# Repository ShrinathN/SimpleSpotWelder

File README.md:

# SimpleSpotWelder
I wanted a spot welder for 18650s so I designed this but then I didn't want a spot welder anymore so I never built it

This welder is designed to do
* Max 55J (more realistically 40J) solders
* Aprox 1000A for 100ms

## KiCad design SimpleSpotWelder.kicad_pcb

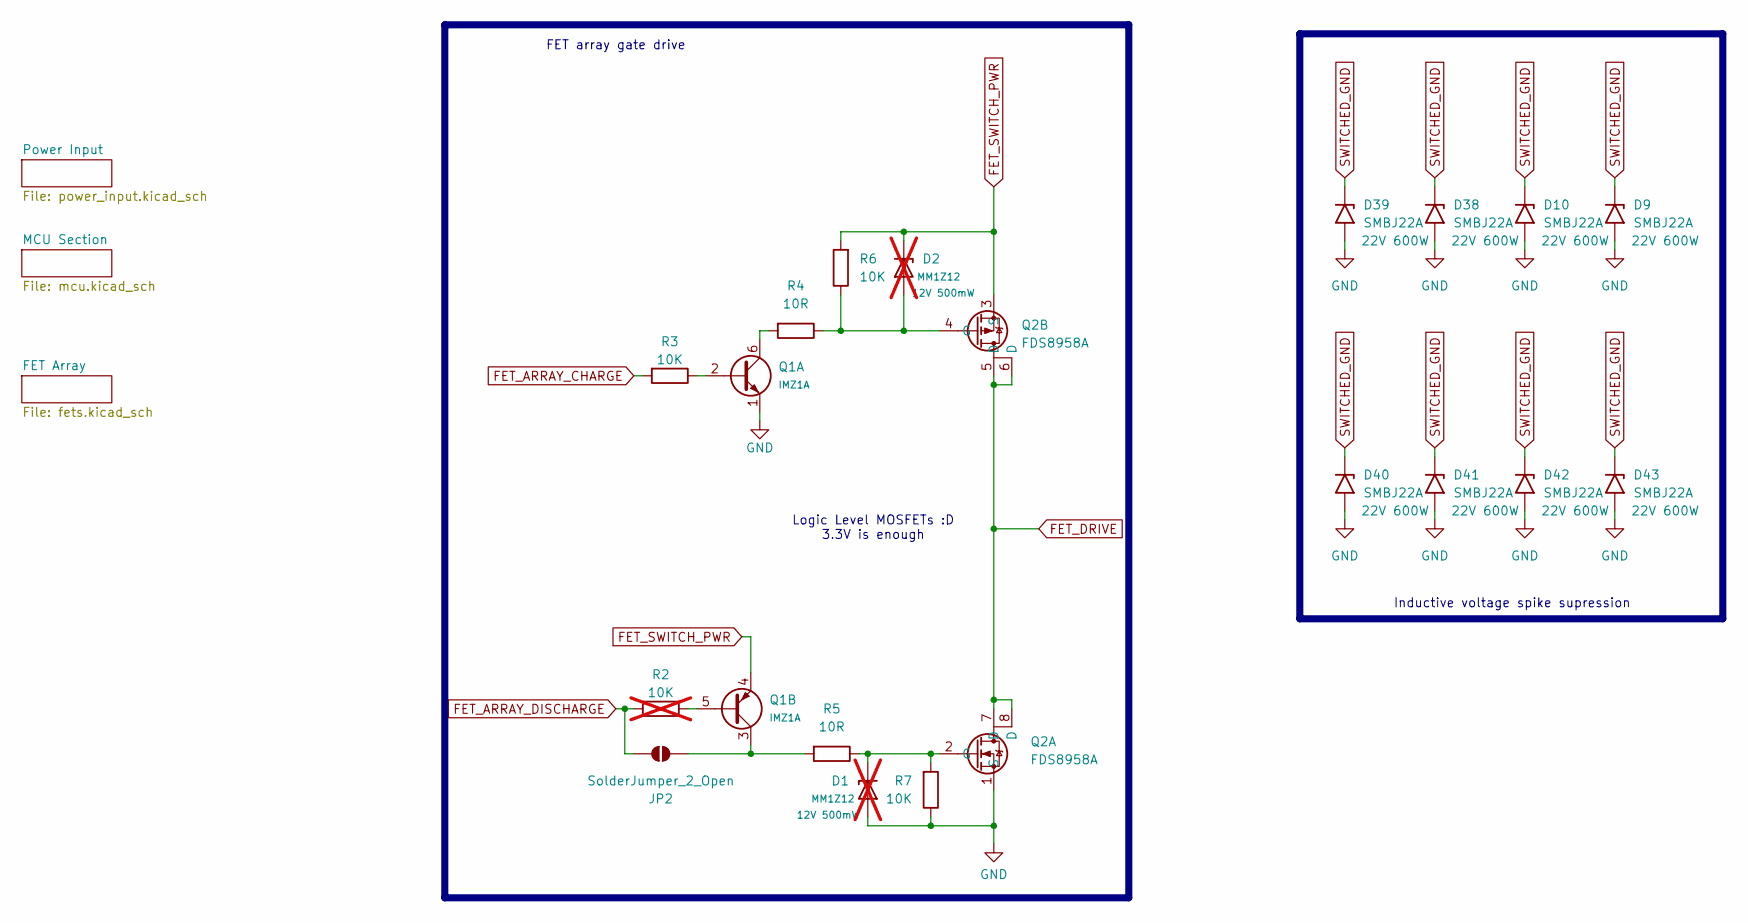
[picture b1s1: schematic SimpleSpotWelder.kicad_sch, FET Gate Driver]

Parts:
D1, D2: MM1Z12; D_SOD-123; Rating 12V 500mW; not fitted
D9, D10, D38, D39, D40, D41, D42, D43: SMBJ22A; D_SMB; Rating 22V 600W
JP2: SolderJumper_2_Open; SolderJumper-2_P1.3mm_Open_Pad1.0x1.5mm
Q1: IMZ1A; SOT-23-6
Q2: FDS8958A; SO-8_3.9x4.9mm_P1.27mm
R2: 10K; R_0805_2012Metric; not fitted
R3, R6, R7: 10K; R_0805_2012Metric
R4, R5: 10R; R_0805_2012Metric

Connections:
FET_ARRAY_CHARGE: R3.2; also elsewhere on the board
FET_ARRAY_DISCHARGE: JP2.2 (B), R2.2; also elsewhere on the board
FET_DRIVE: Q2.5 (D), Q2.6 (D), Q2.7 (D), Q2.8 (D); also elsewhere on the board
FET_SWITCH_PWR: D2.1 (K), Q1.4 (E2), Q2.3 (S), R6.2; also elsewhere on the board
GND: D1.2 (A), D9.2 (A2), D10.2 (A2), D38.2 (A2), D39.2 (A2), D40.2 (A2), D41.2 (A2), D42.2 (A2), D43.2 (A2), Q1.1 (E1), Q2.1 (S), R7.1; also elsewhere on the board
unnamed: D1.1 (K), Q2.2 (G), R5.1, R7.2
unnamed: D2.2 (A), Q2.4 (G), R4.1, R6.1
unnamed: JP2.1 (A), Q1.3 (C2), R5.2
unnamed: Q1.2 (B1), R3.1
unnamed: Q1.6 (C1), R4.2
unnamed: Q1.5 (B2), R2.1
SWITCHED_GND: D9.1 (A1), D10.1 (A1), D38.1 (A1), D39.1 (A1), D40.1 (A1), D41.1 (A1), D42.1 (A1), D43.1 (A1); also elsewhere on the board

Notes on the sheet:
Logic Level MOSFETs :D 3.3V is enough
Inductive voltage spike supression
FET array gate drive

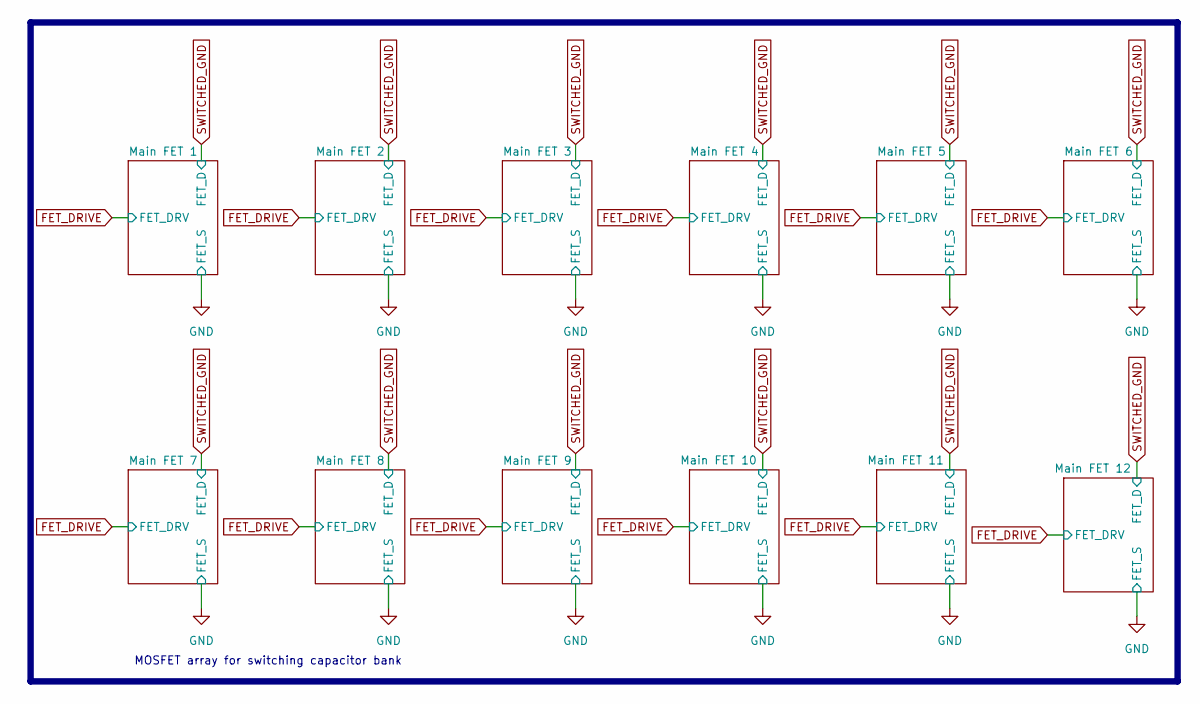
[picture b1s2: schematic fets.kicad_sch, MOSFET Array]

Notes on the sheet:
MOSFET array for switching capacitor bank

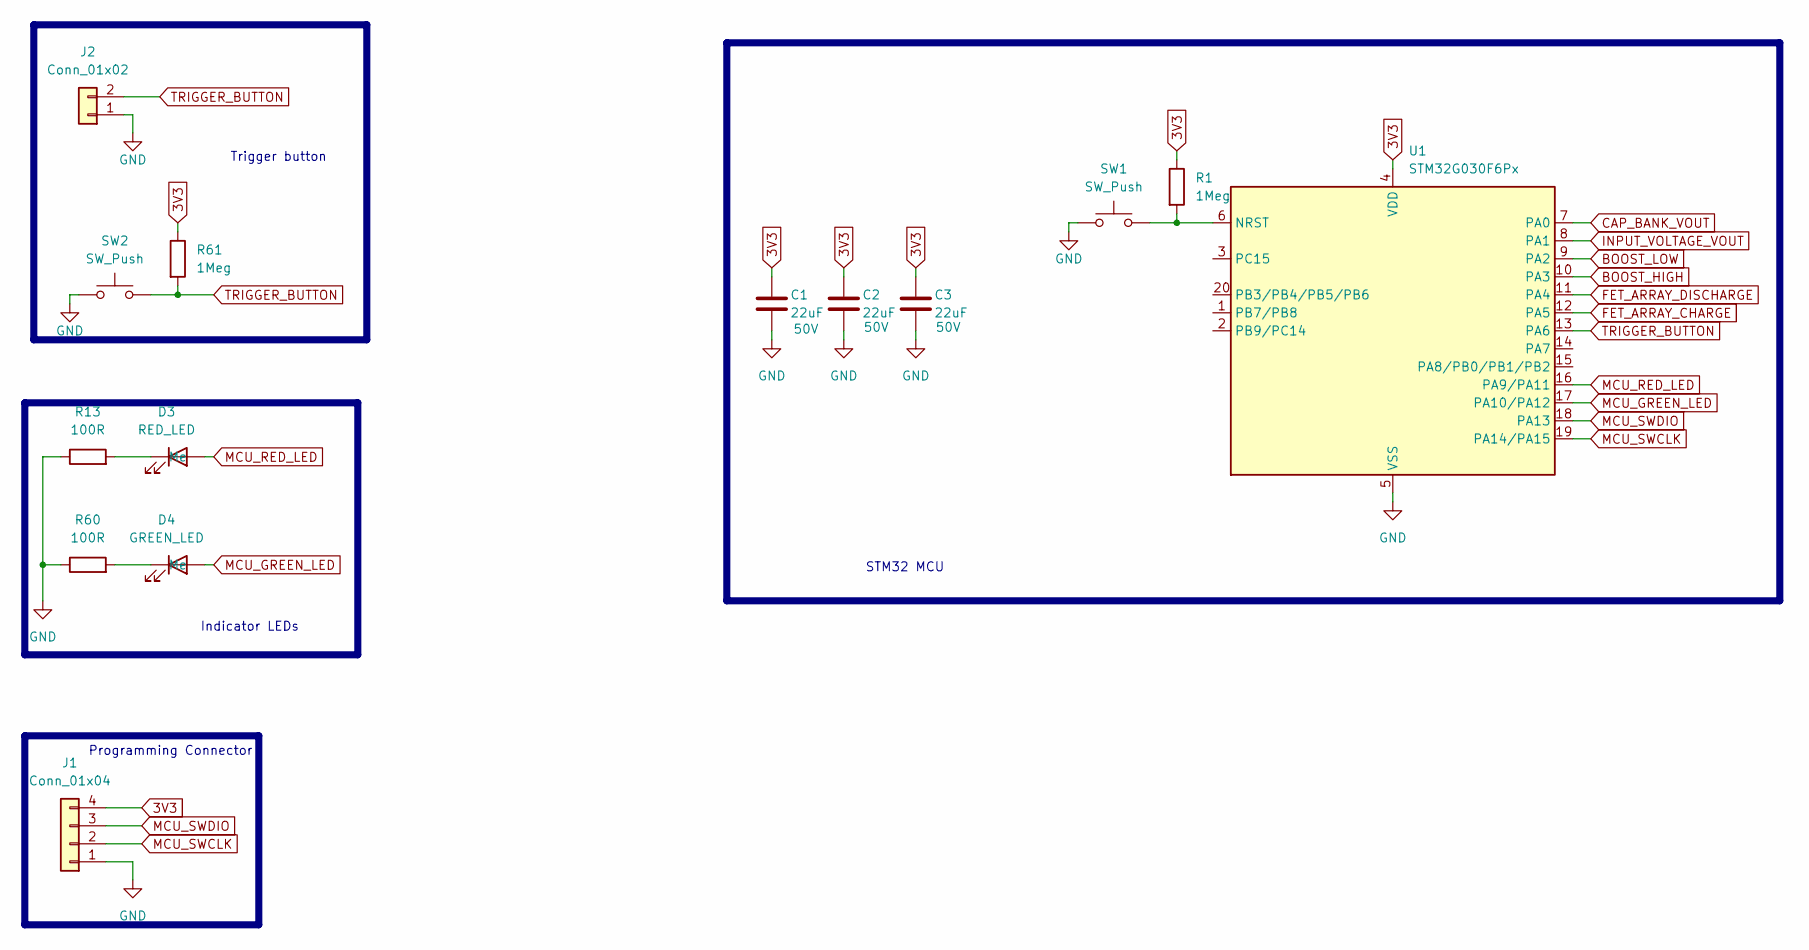
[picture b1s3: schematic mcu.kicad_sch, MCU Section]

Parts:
C1, C2, C3: 22uF; C_0805_2012Metric; Rating 50V
D3: RED_LED; LED_0805_2012Metric
D4: GREEN_LED; LED_0805_2012Metric
J1: Conn_01x04; PinSocket_1x04_P2.54mm_Vertical
J2: Conn_01x02; PinSocket_1x02_P2.54mm_Vertical
R1, R61: 1Meg; R_0805_2012Metric
R13, R60: 100R; R_0805_2012Metric
SW1, SW2: SW_Push; SW_Push_1P1T_XKB_TS-1187A
U1: STM32G030F6Px; TSSOP-20_4.4x6.5mm_P0.65mm

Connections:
3V3: C1.1, C2.1, C3.1, J1.4, R1.1, R61.1, U1.4 (VDD); also elsewhere on the board
BOOST_HIGH: U1.10 (PA3); also elsewhere on the board
BOOST_LOW: U1.9 (PA2); also elsewhere on the board
CAP_BANK_VOUT: U1.7 (PA0); also elsewhere on the board
FET_ARRAY_CHARGE: U1.12 (PA5); also elsewhere on the board
FET_ARRAY_DISCHARGE: U1.11 (PA4); also elsewhere on the board
GND: C1.2, C2.2, C3.2, J1.1, J2.1, R13.1, R60.1, SW1.1, SW2.1, U1.5 (VSS); also elsewhere on the board
INPUT_VOLTAGE_VOUT: U1.8 (PA1); also elsewhere on the board
MCU_GREEN_LED: D4.2 (A), U1.17 (PA10/PA12)
MCU_RED_LED: D3.2 (A), U1.16 (PA9/PA11)
MCU_SWCLK: J1.2, U1.19 (PA14/PA15)
MCU_SWDIO: J1.3, U1.18 (PA13)
unnamed: D3.1 (K), R13.2
unnamed: D4.1 (K), R60.2
unnamed: R1.2, SW1.2, U1.6 (NRST)
TRIGGER_BUTTON: J2.2, R61.2, SW2.2, U1.13 (PA6)

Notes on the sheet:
STM32 MCU
Indicator LEDs
Programming Connector
Trigger button

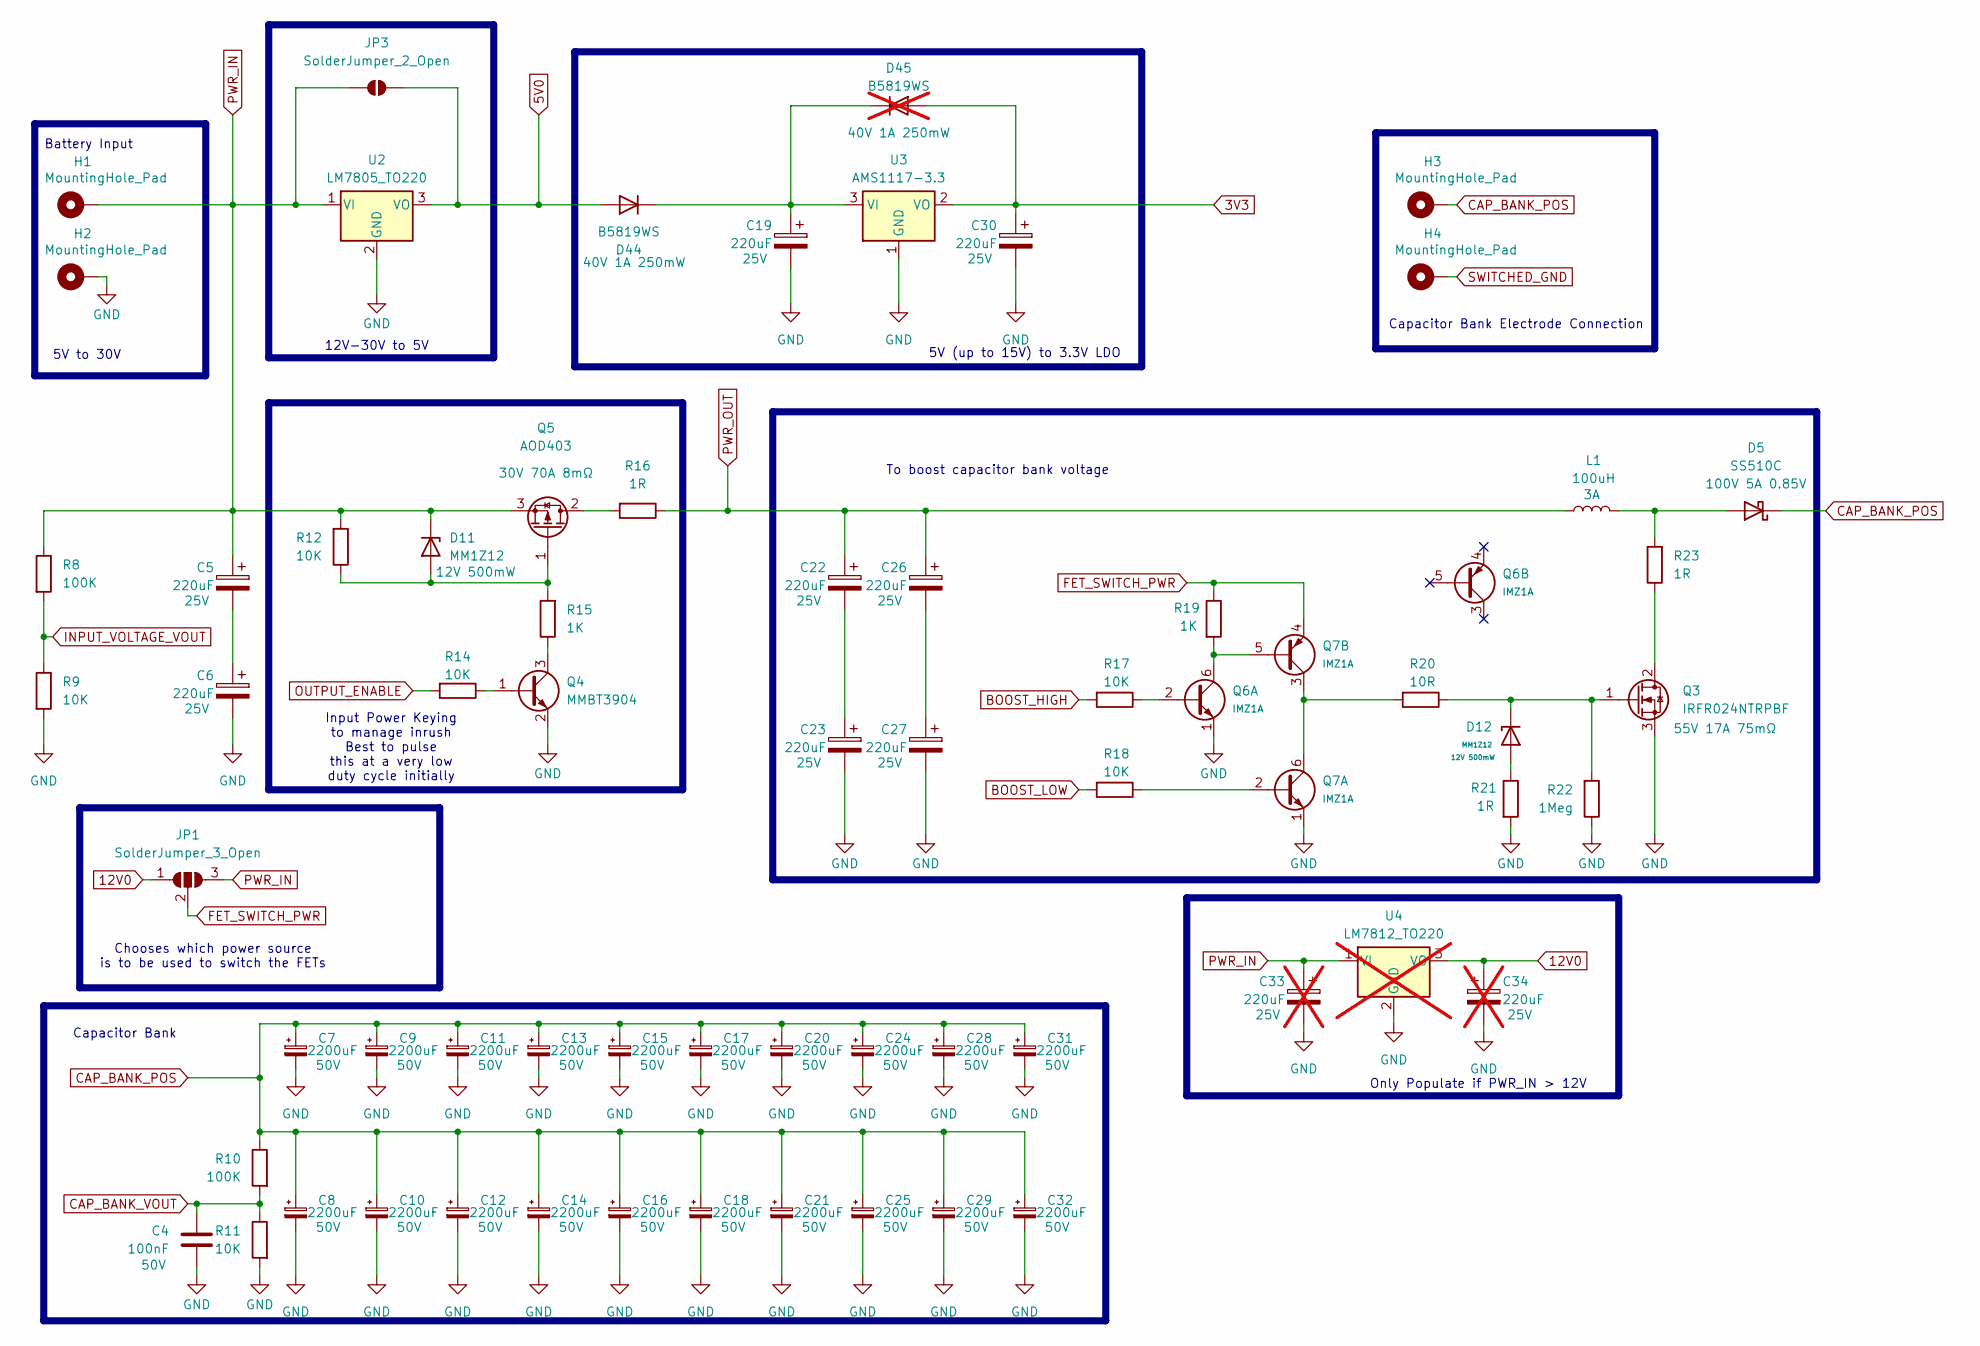
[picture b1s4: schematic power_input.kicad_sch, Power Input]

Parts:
C4: 100nF; C_0805_2012Metric; Rating 50V
C5, C6, C19, C22, C23, C26, C27, C30: 220uF; CP_Radial_D5.0mm_P2.00mm; Rating 25V
C7, C8, C9, C10, C11, C12, C13, C14, C15, C16, C17, C18, C20, C21, C24, C25, C28, C29, C31, C32: 2200uF; CP_Radial_D18.0mm_P7.50mm; Rating 50V
C33, C34: 220uF; CP_Radial_D5.0mm_P2.00mm; Rating 25V; not fitted
D5: SS510C; D_SMC; Rating 100V 5A 0.85V
D11, D12: MM1Z12; D_SOD-123; Rating 12V 500mW
D44: B5819WS; D_SOD-323; Rating 40V 1A 250mW
D45: B5819WS; D_SOD-323; Rating 40V 1A 250mW; not fitted
H1, H2, H3, H4: MountingHole_Pad; MountingHole_3.2mm_M3_Pad_Via
JP1: SolderJumper_3_Open; SolderJumper-3_P2.0mm_Open_TrianglePad1.0x1.5mm
JP3: SolderJumper_2_Open; SolderJumper-2_P1.3mm_Open_Pad1.0x1.5mm
L1: 100uH; L_Coilcraft_MSS1278H-XXX; Rating 3A
Q3: IRFR024NTRPBF; TO-252-2; Rating 55V 17A 75mΩ
Q4: MMBT3904; SOT-23
Q5: AOD403; TO-252-2; Rating 30V 70A 8mΩ
Q6, Q7: IMZ1A; SOT-23-6
R8, R10: 100K; R_0805_2012Metric
R9, R11, R12, R14, R17, R18: 10K; R_0805_2012Metric
R15, R19: 1K; R_0805_2012Metric
R16, R21, R23: 1R; R_0805_2012Metric
R20: 10R; R_0805_2012Metric
R22: 1Meg; R_0805_2012Metric
U2: LM7805_TO220; TO-220-3_Vertical
U3: AMS1117-3.3; SOT-223-3_TabPin2
U4: LM7812_TO220; TO-220-3_Vertical; not fitted

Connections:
3V3: C30.1, D45.2 (A), U3.2 (VO); also elsewhere on the board
5V0: D44.2 (A), JP3.2 (B), U2.3 (VO)
12V0: C34.1, JP1.1 (A), U4.3 (VO)
BOOST_HIGH: R17.2; also elsewhere on the board
BOOST_LOW: R18.2; also elsewhere on the board
CAP_BANK_POS: C7.1, C8.1, C9.1, C10.1, C11.1, C12.1, C13.1, C14.1, C15.1, C16.1, C17.1, C18.1, C20.1, C21.1, C24.1, C25.1, C28.1, C29.1, C31.1, C32.1, D5.1 (K), H3.1, R10.1
CAP_BANK_VOUT: C4.1, R10.2, R11.1; also elsewhere on the board
FET_SWITCH_PWR: JP1.2 (C), Q7.4 (E2), R19.1; also elsewhere on the board
GND: C4.2, C6.2, C7.2, C8.2, C9.2, C10.2, C11.2, C12.2, C13.2, C14.2, C15.2, C16.2, C17.2, C18.2, C19.2, C20.2, C21.2, C23.2, C24.2, C25.2, C27.2, C28.2, C29.2, C30.2, C31.2, C32.2, C33.2, C34.2, H2.1, Q3.3 (S), Q4.2 (E), Q6.1 (E1), Q7.1 (E1), R9.2, R11.2, R21.2, R22.1, U2.2 (GND), U3.1 (GND), U4.2 (GND); also elsewhere on the board
INPUT_VOLTAGE_VOUT: R8.2, R9.1; also elsewhere on the board
unnamed: C5.2, C6.1
unnamed: C22.2, C23.1
unnamed: C26.2, C27.1
unnamed: D5.2 (A), L1.2, R23.2
unnamed: D11.2 (A), Q5.1 (G), R12.1, R15.2
unnamed: D12.2 (A), R21.1
unnamed: D12.1 (K), Q3.1 (G), R20.1, R22.2
unnamed: C19.1, D44.1 (K), D45.1 (K), U3.3 (VI)
unnamed: Q3.2 (D), R23.1
unnamed: Q4.1 (B), R14.1
unnamed: Q4.3 (C), R15.1
unnamed: Q5.2 (D), R16.2
unnamed: Q6.2 (B1), R17.1
unnamed: Q6.6 (C1), Q7.5 (B2), R19.2
unnamed: Q7.2 (B1), R18.1
unnamed: Q7.3 (C2), Q7.6 (C1), R20.2
OUTPUT_ENABLE: R14.2
PWR_IN: C5.1, C33.1, D11.1 (K), H1.1, JP1.3 (B), JP3.1 (A), Q5.3 (S), R8.1, R12.2, U2.1 (VI), U4.1 (VI)
PWR_OUT: C22.1, C26.1, L1.1, R16.1
SWITCHED_GND: H4.1; also elsewhere on the board

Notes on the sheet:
Only Populate if PWR_IN > 12V
5V (up to 15V) to 3.3V LDO
To boost capacitor bank voltage
Battery Input
12V-30V to 5V
Capacitor Bank
Input Power Keying to manage inrush Best to pulse this at a very low duty cycle initially
Chooses which power source is to be used to switch the FETs
Capacitor Bank Electrode Connection
5V to 30V

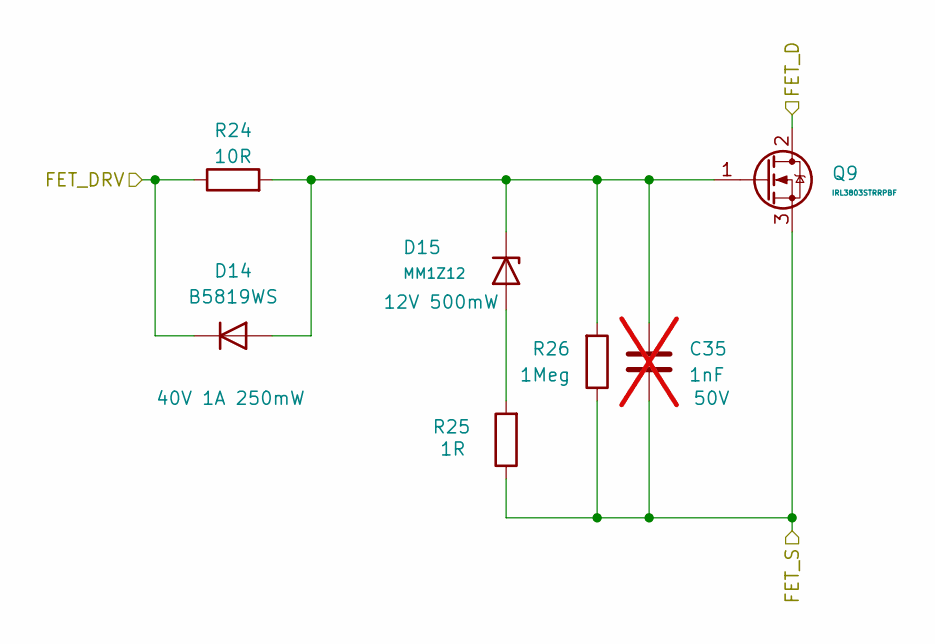
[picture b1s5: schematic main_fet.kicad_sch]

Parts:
C35: 1nF; C_0805_2012Metric; Rating 50V; not fitted
D14: B5819WS; D_SOD-323; Rating 40V 1A 250mW
D15: MM1Z12; D_SOD-123; Rating 12V 500mW
Q9: IRL3803STRRPBF; TO-263-2
R24: 10R; R_0805_2012Metric
R25: 1R; R_0805_2012Metric
R26: 1Meg; R_0805_2012Metric

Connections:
FET_DRIVE: D14.1 (K), R24.1; also elsewhere on the board
GND: C35.2, Q9.3 (S), R25.1, R26.1; also elsewhere on the board
unnamed: C35.1, D14.2 (A), D15.1 (K), Q9.1 (G), R24.2, R26.2
unnamed: D15.2 (A), R25.2
SWITCHED_GND: Q9.2 (D); also elsewhere on the board

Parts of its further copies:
C36, C37, C38, C39, C40, C41, C42, C43, C44, C45, C46: 1nF; C_0805_2012Metric; Rating 50V; not fitted
D16, D18, D20, D22, D24, D26, D28, D30, D32, D34, D36: B5819WS; D_SOD-323; Rating 40V 1A 250mW
D17, D19, D21, D23, D25, D27, D29, D31, D33, D35, D37: MM1Z12; D_SOD-123; Rating 12V 500mW
Q10, Q11, Q12, Q13, Q14, Q15, Q16, Q17, Q18, Q19, Q20: IRL3803STRRPBF; TO-263-2
R27, R30, R33, R36, R39, R42, R45, R48, R51, R54, R57: 10R; R_0805_2012Metric
R28, R31, R34, R37, R40, R43, R46, R49, R52, R55, R58: 1R; R_0805_2012Metric
R29, R32, R35, R38, R41, R44, R47, R50, R53, R56, R59: 1Meg; R_0805_2012Metric

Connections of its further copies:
FET_DRIVE: D16.1 (K), D18.1 (K), D20.1 (K), D22.1 (K), D24.1 (K), D26.1 (K), D28.1 (K), D30.1 (K), D32.1 (K), D34.1 (K), D36.1 (K), R27.1, R30.1, R33.1, R36.1, R39.1, R42.1, R45.1, R48.1, R51.1, R54.1, R57.1; also elsewhere on the board
GND: C36.2, C37.2, C38.2, C39.2, C40.2, C41.2, C42.2, C43.2, C44.2, C45.2, C46.2, Q10.3 (S), Q11.3 (S), Q12.3 (S), Q13.3 (S), Q14.3 (S), Q15.3 (S), Q16.3 (S), Q17.3 (S), Q18.3 (S), Q19.3 (S), Q20.3 (S), R28.1, R29.1, R31.1, R32.1, R34.1, R35.1, R37.1, R38.1, R40.1, R41.1, R43.1, R44.1, R46.1, R47.1, R49.1, R50.1, R52.1, R53.1, R55.1, R56.1, R58.1, R59.1; also elsewhere on the board
unnamed: C36.1, D16.2 (A), D17.1 (K), Q10.1 (G), R27.2, R29.2
unnamed: D17.2 (A), R28.2
unnamed: C37.1, D18.2 (A), D19.1 (K), Q11.1 (G), R30.2, R32.2
unnamed: D19.2 (A), R31.2
unnamed: C38.1, D20.2 (A), D21.1 (K), Q12.1 (G), R33.2, R35.2
unnamed: D21.2 (A), R34.2
unnamed: C39.1, D22.2 (A), D23.1 (K), Q13.1 (G), R36.2, R38.2
unnamed: D23.2 (A), R37.2
unnamed: C40.1, D24.2 (A), D25.1 (K), Q14.1 (G), R39.2, R41.2
unnamed: D25.2 (A), R40.2
unnamed: C41.1, D26.2 (A), D27.1 (K), Q15.1 (G), R42.2, R44.2
unnamed: D27.2 (A), R43.2
unnamed: C42.1, D28.2 (A), D29.1 (K), Q16.1 (G), R45.2, R47.2
unnamed: D29.2 (A), R46.2
unnamed: C43.1, D30.2 (A), D31.1 (K), Q17.1 (G), R48.2, R50.2
unnamed: D31.2 (A), R49.2
unnamed: C44.1, D32.2 (A), D33.1 (K), Q18.1 (G), R51.2, R53.2
unnamed: D33.2 (A), R52.2
unnamed: C45.1, D34.2 (A), D35.1 (K), Q19.1 (G), R54.2, R56.2
unnamed: D35.2 (A), R55.2
unnamed: C46.1, D36.2 (A), D37.1 (K), Q20.1 (G), R57.2, R59.2
unnamed: D37.2 (A), R58.2
SWITCHED_GND: Q10.2 (D), Q11.2 (D), Q12.2 (D), Q13.2 (D), Q14.2 (D), Q15.2 (D), Q16.2 (D), Q17.2 (D), Q18.2 (D), Q19.2 (D), Q20.2 (D); also elsewhere on the board

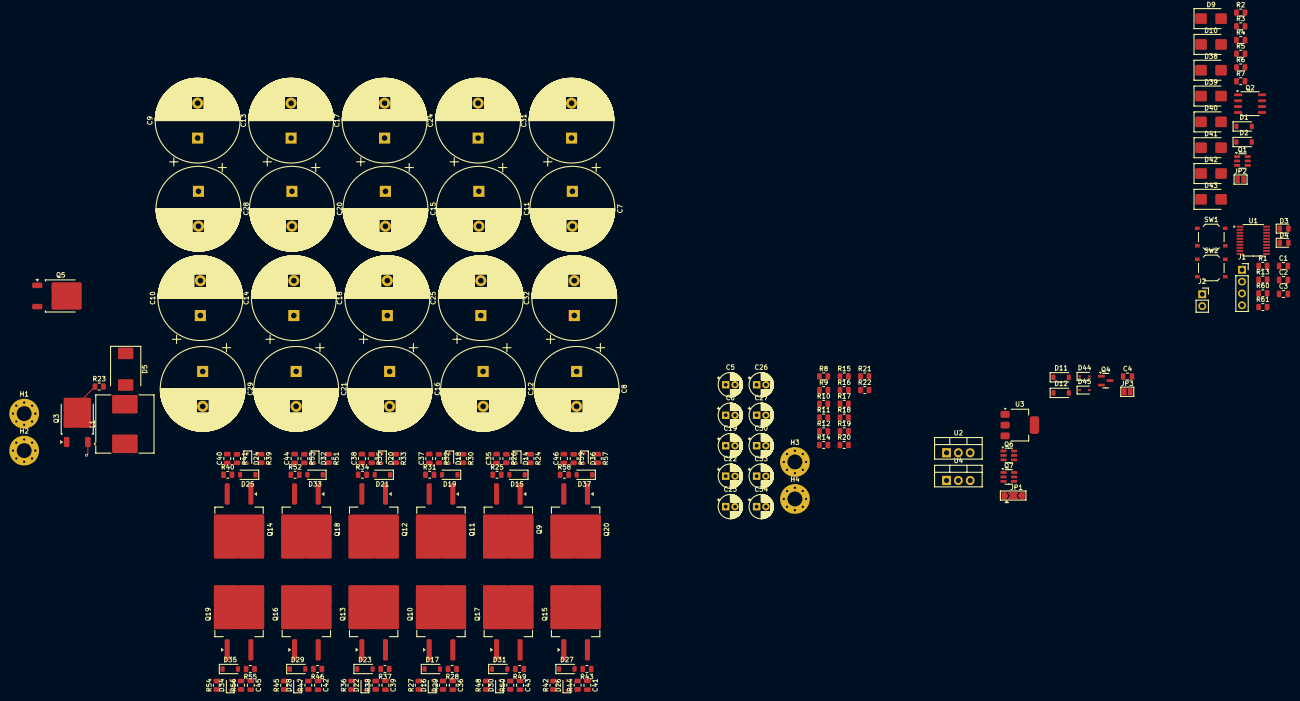
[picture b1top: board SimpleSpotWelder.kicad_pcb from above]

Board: 2 copper layers, 183 parts (0 on the bottom side), 70 nets.

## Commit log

2025-05-04 Added files. Hope I make this sometime in the future
2025-05-04 Added log...
